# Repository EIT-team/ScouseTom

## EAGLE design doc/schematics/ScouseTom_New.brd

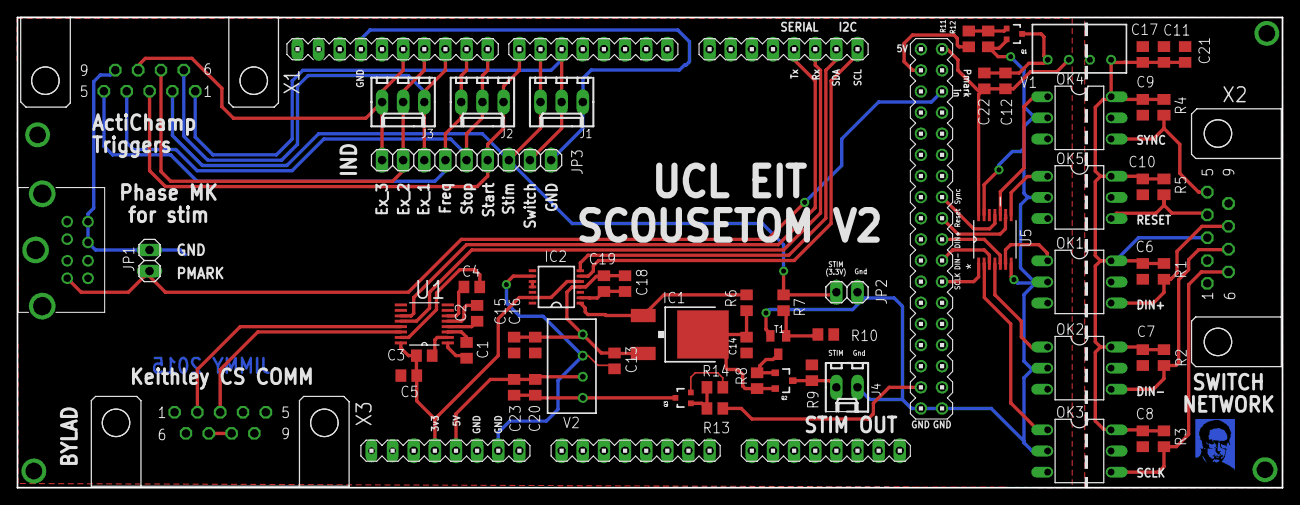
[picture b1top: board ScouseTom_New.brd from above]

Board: 2 copper layers, 152.0 x 56.5 mm, 64 parts (0 on the bottom side), 55 nets.

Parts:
C1, C2, C3, C4, C5, C6, C7, C8, C9, C10, C12, C13, C16, C17, C18, C20: 0.1uF; C0805
C11, C15, C21: 47uF; C0805
C14: 1uF; C0805
C19, C22, C23: 10uF; C0805
DIN8: CS_TRIGGERLINK; DIN8
DUE: DUE(NOMID)
IC1: LM317MBDT; DPACK
IC2: AD5280; TSSOP14
J1: Ind main; 6410-03
J2: Ind Ex1; 6410-03
J3: Ind Ex2; 6410-03
J4: Stim out; 6410-02
JP1: PMARK; 1X02
JP2: Ext Stim; 1X02
JP3: IND_BK; 1X09
OK1, OK2, OK3, OK4, OK5: H11L3M; DIL06
Q1, Q3: FDV303N; SOT323
Q2: FDN304P; SOT23-3
R1, R2, R3: 270; R0805
R4, R5: 270; M0805
R6: 470; R0805
R7: 33k; R0805
R8: 5K1; R0805
R9: 3k; R0805
R10, R12, R14: 10k; R0805
R11, R13: 330; R0805
T1: BC817; SOT23-BEC
U1: ADM3202ARUZ; SOP65P640X120-16N
U5: SN74HCT14PWT; SOP65P640X120-14N
V1: TME0505S; TME
V2: TME1205S; TME
X1: IND DSUB; DSUB9
X2: SW DSUB; DSUB9
X3: CS DSUB; DSUB9

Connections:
5VA: C6.1, C7.1, C8.1, C9.1, C10.1, C11.1, C17.2, C21.1, OK1.6, OK2.6, OK3.6, OK4.6, OK5.6, R1.2, R2.2, R3.2, R4.2, R5.2, V1.4, X2.3
5V_SIDE: C20.2, C23.1, DUE.5V, V2.2
+3V3: C3.1, C5.1, DUE.3V3, IC2.5, IC2.13, U1.16
+5V: C12.2, C22.1, DUE.5V_B, U5.14, V1.2
AGND: C6.2, C7.2, C8.2, C9.2, C10.2, C11.2, C17.1, C21.2, OK1.5, OK2.5, OK3.5, OK4.5, OK5.5, V1.3, X2.2
CS_PMARK: DIN8.3, DUE.25, JP1.2
DIN+: OK1.4, R1.1, X2.8
DIN+_ARD: DUE.39, U5.5
DIN+_INV: OK1.1, U5.6
DIN-: OK2.4, R2.1, X2.7
DIN-_ARD: DUE.41, U5.3
DIN-_INV: OK2.1, U5.4
GND: C4.2, C5.2, C13.1, C14.1, C15.2, C16.1, C18.1, C19.2, DIN8.7, DIN8.8, DUE.GND1, DUE.GND_1, DUE.GND_2, DUE.GND_A, DUE.GND_B, IC2.2, IC2.8, IC2.9, IC2.10, IC2.11, J1.3, J4.2, JP1.1, JP2.2, JP3.9, OK1.2, OK2.2, OK3.2, OK4.2, OK5.2, Q1.2, Q3.2, R9.1, R10.1, R12.1, R14.1, T1.E, U1.15, U5.7, U5.13, V2.3, X1.9, X3.5
IND_EX_1: DUE.10, J3.3, JP3.3, X1.6
IND_EX_2: DUE.11, J3.2, JP3.2, X1.7
IND_EX_3: DUE.12, J3.1, JP3.1, X1.8
IND_FREQ: DUE.9, J2.1, JP3.4, X1.5
IND_START: DUE.7, J2.3, JP3.6, X1.3
IND_STIM: DUE.6, J1.1, JP2.1, JP3.7, R7.1, X1.2
IND_STOP: DUE.8, J2.2, JP3.5, X1.4
IND_SWITCH: DUE.5, J1.2, JP3.8, X1.1
unnamed: R7.2, R10.2, T1.B
unnamed: Q1.1, R11.1, R12.2
unnamed: Q2.1, R8.2, T1.C
unnamed: X3.7, X3.8
unnamed: Q3.1, R13.1, R14.2
unnamed: C1.2, U1.1
unnamed: C1.1, U1.3
unnamed: C2.2, U1.4
unnamed: C2.1, U1.5
unnamed: C3.2, U1.2
unnamed: C4.1, U1.6
POT_IN: IC1.1, IC2.1, R6.2
PWR_STIM: DUE.52, R13.2
PWR_SWITCH: DUE.22, R11.2
RESET: OK5.4, R5.1, X2.4
RESET_ARD: DUE.37, U5.9
RESET_INV: OK5.1, U5.8
RS232_RXD: U1.14, X3.3
RS232_TXD: U1.13, X3.2
SCL: DUE.SCL, IC2.6
SCLK: OK3.4, R3.1, X2.6
SCLK_ARD: DUE.43, U5.1
SCLK_INV: OK3.1, U5.2
SDA: DUE.SDA, IC2.7
STIM_OUT: J4.1, Q2.3, R9.2
STIM_REG_VIN-: C20.1, C23.2, Q3.3, V2.1
SW_REG_VIN-: C12.1, C22.2, Q1.3, V1.1
SYNC: OK4.4, R4.1, X2.5
SYNC_ARD: DUE.35, U5.11
SYNC_INV: OK4.1, U5.10
TTL_RX: DUE.RX1, U1.12
TTL_TX: DUE.TX1, U1.11
V_STIM: C14.2, IC1.4, Q2.2, R6.1, R8.1
V_STIM_REF: C13.2, C15.1, C16.2, C18.2, C19.1, IC1.3, IC2.4, V2.4

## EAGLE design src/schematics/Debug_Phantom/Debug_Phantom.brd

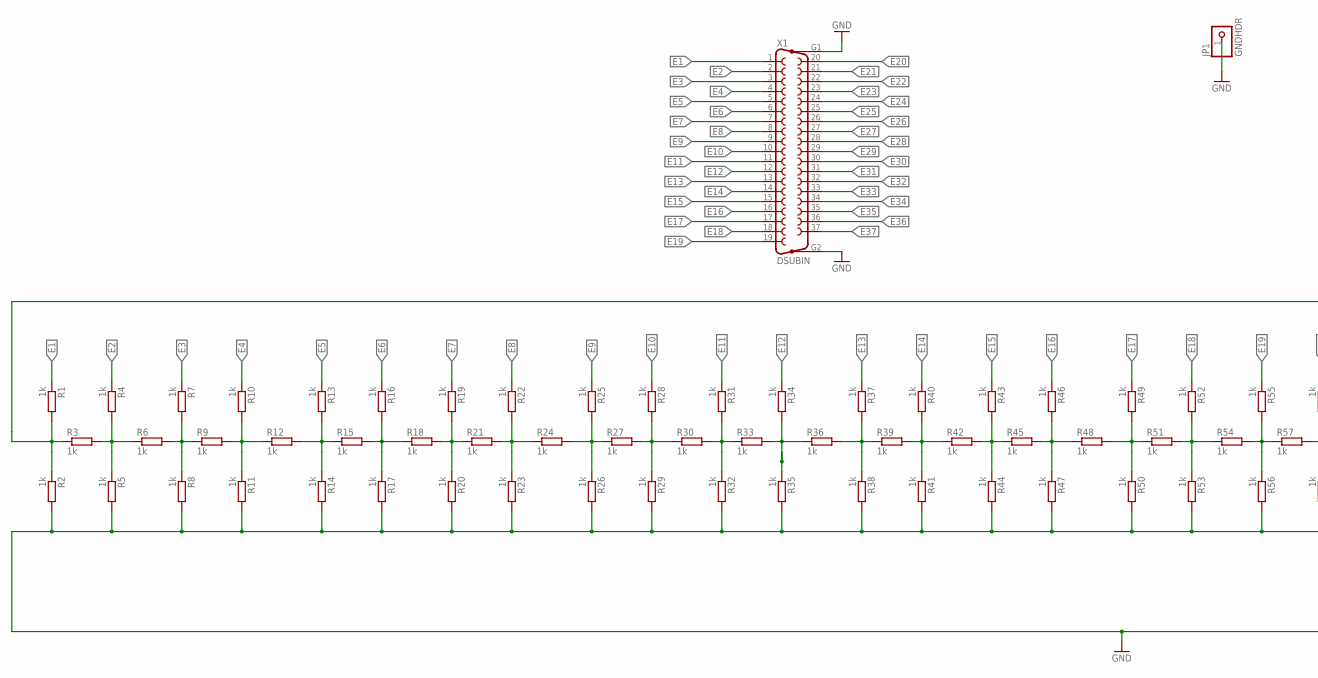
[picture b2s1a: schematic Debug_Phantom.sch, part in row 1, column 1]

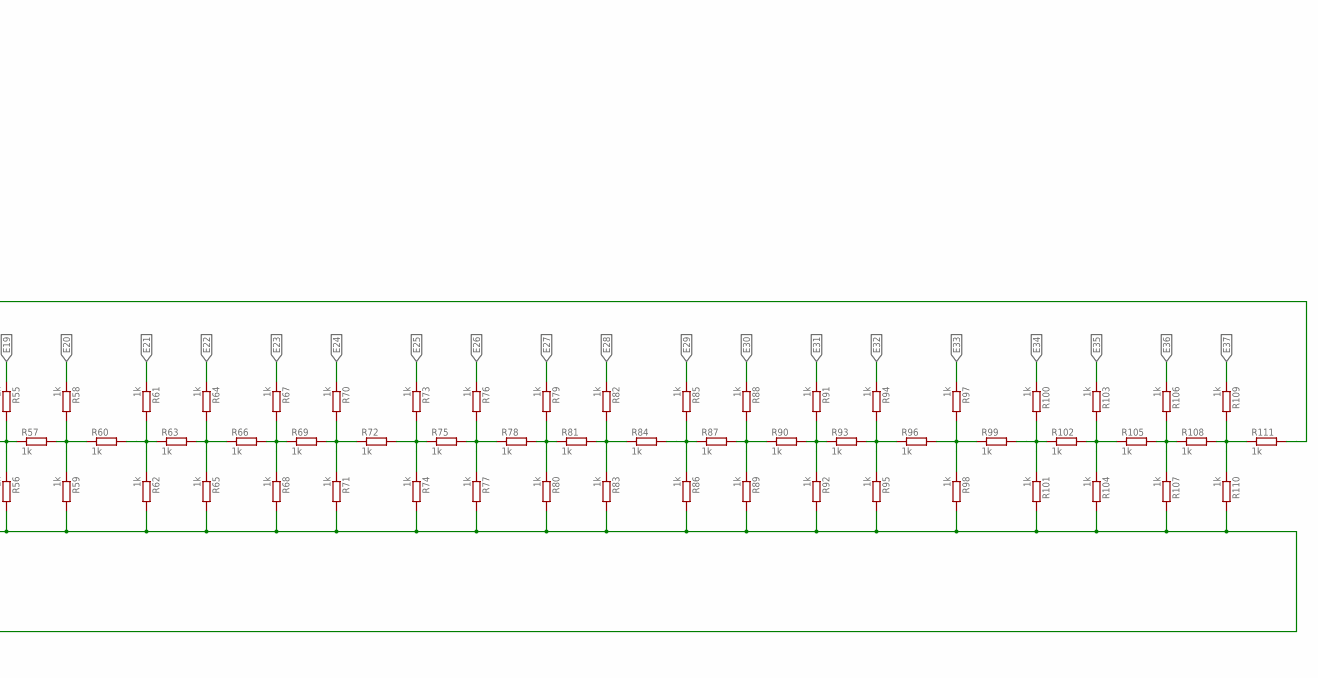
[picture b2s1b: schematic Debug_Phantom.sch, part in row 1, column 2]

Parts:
JP1: GNDHDR; 1X01
R1, R2, R3, R4, R5, R6, R7, R8, R9, R10, R11, R12, R13, R14, R15, R16, R17, R18, R19, R20, R21, R22, R23, R24, R25, R26, R27, R28, R29, R30, R31, R32, R33, R34, R35, R36, R37, R38, R39, R40, R41, R42, R43, R44, R45, R46, R47, R48, R49, R50, R51, R52, R53, R54, R55, R56, R57, R58, R59, R60, R61, R62, R63, R64, R65, R66, R67, R68, R69, R70, R71, R72, R73, R74, R75, R76, R77, R78, R79, R80, R81, R82, R83, R84, R85, R86, R87, R88, R89, R90, R91, R92, R93, R94, R95, R96, R97, R98, R99, R100, R101, R102, R103, R104, R105, R106, R107, R108, R109, R110, R111: 1k; R0402
X1: DSUBIN; F37VP

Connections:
E1: R1.1, X1.1
E2: R4.1, X1.2
E3: R7.1, X1.3
E4: R10.1, X1.4
E5: R13.1, X1.5
E6: R16.1, X1.6
E7: R19.1, X1.7
E8: R22.1, X1.8
E9: R25.1, X1.9
E10: R28.1, X1.10
E11: R31.1, X1.11
E12: R34.1, X1.12
E13: R37.1, X1.13
E14: R40.1, X1.14
E15: R43.1, X1.15
E16: R46.1, X1.16
E17: R49.1, X1.17
E18: R52.1, X1.18
E19: R55.1, X1.19
E20: R58.1, X1.20
E21: R61.1, X1.21
E22: R64.1, X1.22
E23: R67.1, X1.23
E24: R70.1, X1.24
E25: R73.1, X1.25
E26: R76.1, X1.26
E27: R79.1, X1.27
E28: R82.1, X1.28
E29: R85.1, X1.29
E30: R88.1, X1.30
E31: R91.1, X1.31
E32: R94.1, X1.32
E33: R97.1, X1.33
E34: R100.1, X1.34
E35: R103.1, X1.35
E36: R106.1, X1.36
E37: R109.1, X1.37
E38: R1.2, R2.1, R3.1, R111.2
E39: R3.2, R4.2, R5.1, R6.1
E40: R6.2, R7.2, R8.1, R9.1
E41: R9.2, R10.2, R11.1, R12.1
E42: R12.2, R13.2, R14.1, R15.1
E43: R15.2, R16.2, R17.1, R18.1
E44: R18.2, R19.2, R20.1, R21.1
E45: R21.2, R22.2, R23.1, R24.1
E46: R24.2, R25.2, R26.1, R27.1
E47: R27.2, R28.2, R29.1, R30.1
E48: R30.2, R31.2, R32.1, R33.1
E49: R33.2, R34.2, R35.1, R36.1
E50: R36.2, R37.2, R38.1, R39.1
E51: R39.2, R40.2, R41.1, R42.1
E52: R42.2, R43.2, R44.1, R45.1
E53: R45.2, R46.2, R47.1, R48.1
E54: R48.2, R49.2, R50.1, R51.1
E55: R51.2, R52.2, R53.1, R54.1
E56: R54.2, R55.2, R56.1, R57.1
E57: R57.2, R58.2, R59.1, R60.1
E58: R60.2, R61.2, R62.1, R63.1
E59: R63.2, R64.2, R65.1, R66.1
E60: R66.2, R67.2, R68.1, R69.1
E61: R69.2, R70.2, R71.1, R72.1
E63: R75.2, R76.2, R77.1, R78.1
E64: R78.2, R79.2, R80.1, R81.1
E65: R81.2, R82.2, R83.1, R84.1
E66: R84.2, R85.2, R86.1, R87.1
E67: R87.2, R88.2, R89.1, R90.1
E68: R90.2, R91.2, R92.1, R93.1
E69: R93.2, R94.2, R95.1, R96.1
E70: R96.2, R97.2, R98.1, R99.1
E72: R102.2, R103.2, R104.1, R105.1
E73: R105.2, R106.2, R107.1, R108.1
E74: R108.2, R109.2, R110.1, R111.1
GND: JP1.1, R2.2, R5.2, R8.2, R11.2, R14.2, R17.2, R20.2, R23.2, R26.2, R29.2, R32.2, R35.2, R38.2, R41.2, R44.2, R47.2, R50.2, R53.2, R56.2, R59.2, R62.2, R65.2, R68.2, R71.2, R74.2, R77.2, R80.2, R83.2, R86.2, R89.2, R92.2, R95.2, R98.2, R101.2, R104.2, R107.2, R110.2, X1.G1, X1.G2
unnamed: R72.2, R73.2, R74.1, R75.1
unnamed: R99.2, R100.2, R101.1, R102.1

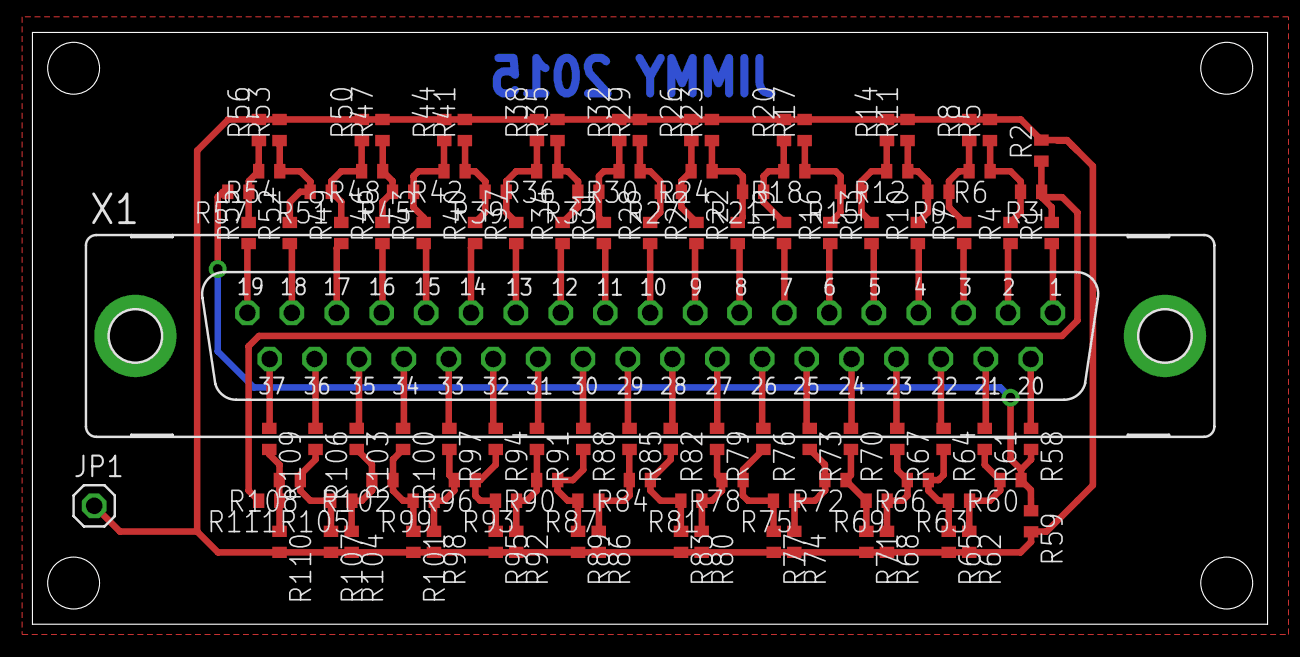
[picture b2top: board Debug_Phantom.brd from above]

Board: 2 copper layers, 76.2 x 36.5 mm, 113 parts (0 on the bottom side), 75 nets.

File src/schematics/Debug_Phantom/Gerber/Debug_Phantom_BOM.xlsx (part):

Part | Value | Device | Package | Description | MPN | OC_FARNELL | PCBTRAINFREE
R1 | 1k | R-EU_R0402 | R0402 | RESISTOR, European symbol | MC00625W040211K | 1358043 | PCBTRAINFREESTOCK
R2 | 1k | R-EU_R0402 | R0402 | RESISTOR, European symbol | MC00625W040211K | 1358043 | PCBTRAINFREESTOCK
R3 | 1k | R-EU_R0402 | R0402 | RESISTOR, European symbol | MC00625W040211K | 1358043 | PCBTRAINFREESTOCK
R4 | 1k | R-EU_R0402 | R0402 | RESISTOR, European symbol | MC00625W040211K | 1358043 | PCBTRAINFREESTOCK
R5 | 1k | R-EU_R0402 | R0402 | RESISTOR, European symbol | MC00625W040211K | 1358043 | PCBTRAINFREESTOCK
R6 | 1k | R-EU_R0402 | R0402 | RESISTOR, European symbol | MC00625W040211K | 1358043 | PCBTRAINFREESTOCK
R7 | 1k | R-EU_R0402 | R0402 | RESISTOR, European symbol | MC00625W040211K | 1358043 | PCBTRAINFREESTOCK
R8 | 1k | R-EU_R0402 | R0402 | RESISTOR, European symbol | MC00625W040211K | 1358043 | PCBTRAINFREESTOCK
R9 | 1k | R-EU_R0402 | R0402 | RESISTOR, European symbol | MC00625W040211K | 1358043 | PCBTRAINFREESTOCK
R10 | 1k | R-EU_R0402 | R0402 | RESISTOR, European symbol | MC00625W040211K | 1358043 | PCBTRAINFREESTOCK
R11 | 1k | R-EU_R0402 | R0402 | RESISTOR, European symbol | MC00625W040211K | 1358043 | PCBTRAINFREESTOCK
R12 | 1k | R-EU_R0402 | R0402 | RESISTOR, European symbol | MC00625W040211K | 1358043 | PCBTRAINFREESTOCK
R13 | 1k | R-EU_R0402 | R0402 | RESISTOR, European symbol | MC00625W040211K | 1358043 | PCBTRAINFREESTOCK
R14 | 1k | R-EU_R0402 | R0402 | RESISTOR, European symbol | MC00625W040211K | 1358043 | PCBTRAINFREESTOCK
R15 | 1k | R-EU_R0402 | R0402 | RESISTOR, European symbol | MC00625W040211K | 1358043 | PCBTRAINFREESTOCK
R16 | 1k | R-EU_R0402 | R0402 | RESISTOR, European symbol | MC00625W040211K | 1358043 | PCBTRAINFREESTOCK
R17 | 1k | R-EU_R0402 | R0402 | RESISTOR, European symbol | MC00625W040211K | 1358043 | PCBTRAINFREESTOCK
R18 | 1k | R-EU_R0402 | R0402 | RESISTOR, European symbol | MC00625W040211K | 1358043 | PCBTRAINFREESTOCK
R19 | 1k | R-EU_R0402 | R0402 | RESISTOR, European symbol | MC00625W040211K | 1358043 | PCBTRAINFREESTOCK
R20 | 1k | R-EU_R0402 | R0402 | RESISTOR, European symbol | MC00625W040211K | 1358043 | PCBTRAINFREESTOCK
R21 | 1k | R-EU_R0402 | R0402 | RESISTOR, European symbol | MC00625W040211K | 1358043 | PCBTRAINFREESTOCK
R22 | 1k | R-EU_R0402 | R0402 | RESISTOR, European symbol | MC00625W040211K | 1358043 | PCBTRAINFREESTOCK
R23 | 1k | R-EU_R0402 | R0402 | RESISTOR, European symbol | MC00625W040211K | 1358043 | PCBTRAINFREESTOCK
R24 | 1k | R-EU_R0402 | R0402 | RESISTOR, European symbol | MC00625W040211K | 1358043 | PCBTRAINFREESTOCK
R25 | 1k | R-EU_R0402 | R0402 | RESISTOR, European symbol | MC00625W040211K | 1358043 | PCBTRAINFREESTOCK
R26 | 1k | R-EU_R0402 | R0402 | RESISTOR, European symbol | MC00625W040211K | 1358043 | PCBTRAINFREESTOCK
R27 | 1k | R-EU_R0402 | R0402 | RESISTOR, European symbol | MC00625W040211K | 1358043 | PCBTRAINFREESTOCK
R28 | 1k | R-EU_R0402 | R0402 | RESISTOR, European symbol | MC00625W040211K | 1358043 | PCBTRAINFREESTOCK
R29 | 1k | R-EU_R0402 | R0402 | RESISTOR, European symbol | MC00625W040211K | 1358043 | PCBTRAINFREESTOCK
R30 | 1k | R-EU_R0402 | R0402 | RESISTOR, European symbol | MC00625W040211K | 1358043 | PCBTRAINFREESTOCK
R31 | 1k | R-EU_R0402 | R0402 | RESISTOR, European symbol | MC00625W040211K | 1358043 | PCBTRAINFREESTOCK
R32 | 1k | R-EU_R0402 | R0402 | RESISTOR, European symbol | MC00625W040211K | 1358043 | PCBTRAINFREESTOCK
R33 | 1k | R-EU_R0402 | R0402 | RESISTOR, European symbol | MC00625W040211K | 1358043 | PCBTRAINFREESTOCK
R34 | 1k | R-EU_R0402 | R0402 | RESISTOR, European symbol | MC00625W040211K | 1358043 | PCBTRAINFREESTOCK
R35 | 1k | R-EU_R0402 | R0402 | RESISTOR, European symbol | MC00625W040211K | 1358043 | PCBTRAINFREESTOCK
R36 | 1k | R-EU_R0402 | R0402 | RESISTOR, European symbol | MC00625W040211K | 1358043 | PCBTRAINFREESTOCK
R37 | 1k | R-EU_R0402 | R0402 | RESISTOR, European symbol | MC00625W040211K | 1358043 | PCBTRAINFREESTOCK
R38 | 1k | R-EU_R0402 | R0402 | RESISTOR, European symbol | MC00625W040211K | 1358043 | PCBTRAINFREESTOCK
R39 | 1k | R-EU_R0402 | R0402 | RESISTOR, European symbol | MC00625W040211K | 1358043 | PCBTRAINFREESTOCK
R40 | 1k | R-EU_R0402 | R0402 | RESISTOR, European symbol | MC00625W040211K | 1358043 | PCBTRAINFREESTOCK
R41 | 1k | R-EU_R0402 | R0402 | RESISTOR, European symbol | MC00625W040211K | 1358043 | PCBTRAINFREESTOCK
R42 | 1k | R-EU_R0402 | R0402 | RESISTOR, European symbol | MC00625W040211K | 1358043 | PCBTRAINFREESTOCK
R43 | 1k | R-EU_R0402 | R0402 | RESISTOR, European symbol | MC00625W040211K | 1358043 | PCBTRAINFREESTOCK
R44 | 1k | R-EU_R0402 | R0402 | RESISTOR, European symbol | MC00625W040211K | 1358043 | PCBTRAINFREESTOCK
R45 | 1k | R-EU_R0402 | R0402 | RESISTOR, European symbol | MC00625W040211K | 1358043 | PCBTRAINFREESTOCK
R46 | 1k | R-EU_R0402 | R0402 | RESISTOR, European symbol | MC00625W040211K | 1358043 | PCBTRAINFREESTOCK
R47 | 1k | R-EU_R0402 | R0402 | RESISTOR, European symbol | MC00625W040211K | 1358043 | PCBTRAINFREESTOCK
R48 | 1k | R-EU_R0402 | R0402 | RESISTOR, European symbol | MC00625W040211K | 1358043 | PCBTRAINFREESTOCK
R49 | 1k | R-EU_R0402 | R0402 | RESISTOR, European symbol | MC00625W040211K | 1358043 | PCBTRAINFREESTOCK
R50 | 1k | R-EU_R0402 | R0402 | RESISTOR, European symbol | MC00625W040211K | 1358043 | PCBTRAINFREESTOCK
R51 | 1k | R-EU_R0402 | R0402 | RESISTOR, European symbol | MC00625W040211K | 1358043 | PCBTRAINFREESTOCK
R52 | 1k | R-EU_R0402 | R0402 | RESISTOR, European symbol | MC00625W040211K | 1358043 | PCBTRAINFREESTOCK
R53 | 1k | R-EU_R0402 | R0402 | RESISTOR, European symbol | MC00625W040211K | 1358043 | PCBTRAINFREESTOCK
R54 | 1k | R-EU_R0402 | R0402 | RESISTOR, European symbol | MC00625W040211K | 1358043 | PCBTRAINFREESTOCK
R55 | 1k | R-EU_R0402 | R0402 | RESISTOR, European symbol | MC00625W040211K | 1358043 | PCBTRAINFREESTOCK
R56 | 1k | R-EU_R0402 | R0402 | RESISTOR, European symbol | MC00625W040211K | 1358043 | PCBTRAINFREESTOCK
R57 | 1k | R-EU_R0402 | R0402 | RESISTOR, European symbol | MC00625W040211K | 1358043 | PCBTRAINFREESTOCK
R58 | 1k | R-EU_R0402 | R0402 | RESISTOR, European symbol | MC00625W040211K | 1358043 | PCBTRAINFREESTOCK
R59 | 1k | R-EU_R0402 | R0402 | RESISTOR, European symbol | MC00625W040211K | 1358043 | PCBTRAINFREESTOCK
R60 | 1k | R-EU_R0402 | R0402 | RESISTOR, European symbol | MC00625W040211K | 1358043 | PCBTRAINFREESTOCK
R61 | 1k | R-EU_R0402 | R0402 | RESISTOR, European symbol | MC00625W040211K | 1358043 | PCBTRAINFREESTOCK
R62 | 1k | R-EU_R0402 | R0402 | RESISTOR, European symbol | MC00625W040211K | 1358043 | PCBTRAINFREESTOCK
R63 | 1k | R-EU_R0402 | R0402 | RESISTOR, European symbol | MC00625W040211K | 1358043 | PCBTRAINFREESTOCK
R64 | 1k | R-EU_R0402 | R0402 | RESISTOR, European symbol | MC00625W040211K | 1358043 | PCBTRAINFREESTOCK
R65 | 1k | R-EU_R0402 | R0402 | RESISTOR, European symbol | MC00625W040211K | 1358043 | PCBTRAINFREESTOCK
R66 | 1k | R-EU_R0402 | R0402 | RESISTOR, European symbol | MC00625W040211K | 1358043 | PCBTRAINFREESTOCK
R67 | 1k | R-EU_R0402 | R0402 | RESISTOR, European symbol | MC00625W040211K | 1358043 | PCBTRAINFREESTOCK
R68 | 1k | R-EU_R0402 | R0402 | RESISTOR, European symbol | MC00625W040211K | 1358043 | PCBTRAINFREESTOCK
R69 | 1k | R-EU_R0402 | R0402 | RESISTOR, European symbol | MC00625W040211K | 1358043 | PCBTRAINFREESTOCK
R70 | 1k | R-EU_R0402 | R0402 | RESISTOR, European symbol | MC00625W040211K | 1358043 | PCBTRAINFREESTOCK
R71 | 1k | R-EU_R0402 | R0402 | RESISTOR, European symbol | MC00625W040211K | 1358043 | PCBTRAINFREESTOCK
R72 | 1k | R-EU_R0402 | R0402 | RESISTOR, European symbol | MC00625W040211K | 1358043 | PCBTRAINFREESTOCK
R73 | 1k | R-EU_R0402 | R0402 | RESISTOR, European symbol | MC00625W040211K | 1358043 | PCBTRAINFREESTOCK
R74 | 1k | R-EU_R0402 | R0402 | RESISTOR, European symbol | MC00625W040211K | 1358043 | PCBTRAINFREESTOCK
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
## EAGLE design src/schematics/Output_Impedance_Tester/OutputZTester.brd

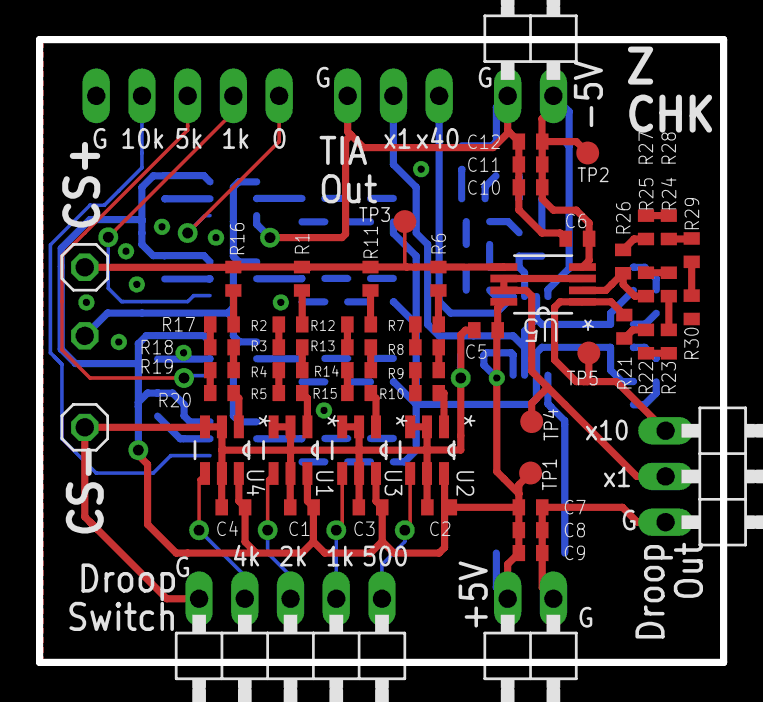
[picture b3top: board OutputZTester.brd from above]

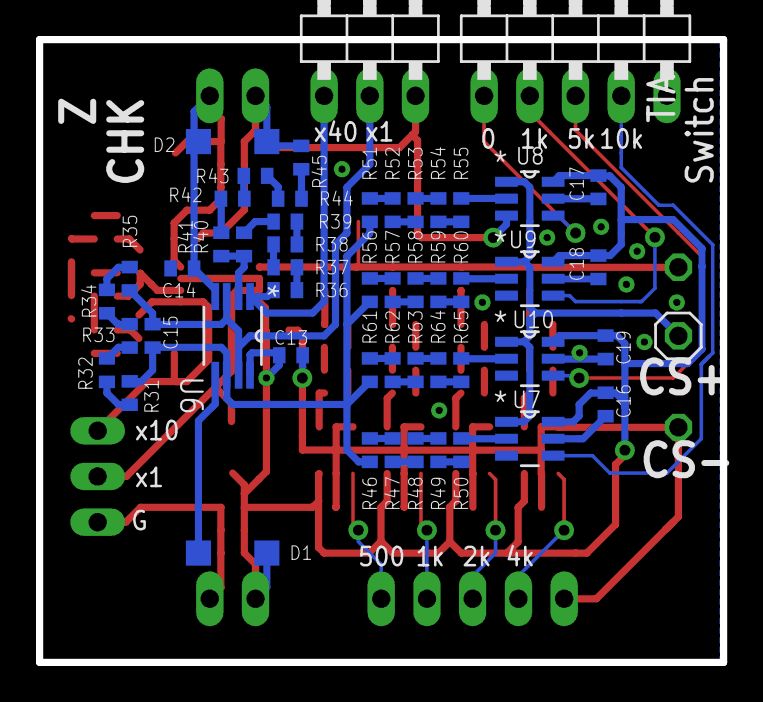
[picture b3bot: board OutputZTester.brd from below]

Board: 2 copper layers, 38.0 x 34.6 mm, 110 parts (52 on the bottom side), 80 nets.

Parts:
C1, C2, C3, C4, C5, C6, C8, C11, C13, C14, C16, C17, C18, C19: 0.1uF; C0402
C7, C10: 2.2uF; C0402
C9, C12: 10nF; C0402
C15: 2.2nF; C0402
D1, D2: 1N4148W-7-F; SOD123
JP1: Droop_out; 1X03/90
JP2: Droop_sw; 1X05/90
JP3: Source; 1X01
JP4: Sink; 1X01
JP5, JP6: PWR_IN; 1X02/90
JP7: Source_TIA; 1X01
JP8: TIA_out; 1X03/90
JP9: TIA_sw; 1X05/90
R1, R3, R5: 430; R0402
R2, R11, R12, R13, R14, R15, R31, R32, R33, R34, R35, R56, R57, R58, R59, R60: 200; R0402
R4: 510; R0402
R6, R7, R8, R9, R10: 100; R0402
R16, R17, R18, R19: 750; R0402
R20: 1000; R0402
R21, R22, R23, R24, R25, R46, R47, R48, R49, R50: 2k; R0402
R26, R27, R28, R29, R30: 20k; R0402
R36, R37, R38, R39, R40: 12k; R0402
R41, R42, R43, R44, R45: 300; R0402
R51, R52, R53, R54, R55: 0; R0402
R61, R62, R63, R64, R65: 1k; R0402
TP1, TP2, TP3, TP4, TP5: TPSB1,27; B1,27
U1, U2, U3, U4, U7, U8, U9, U10: ADG801BRTZ-REEL7; SOT95P280X145-6N
U5, U6: ADA4552-2ARM; SOP65P490X110-8N

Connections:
AGND: C1.1, C2.1, C3.1, C4.1, C5.1, C6.2, C7.2, C8.2, C9.2, C10.2, C11.2, C12.2, C13.1, C14.2, C16.1, C17.1, C18.1, C19.1, D1.A, D2.C, JP1.3, JP2.5, JP4.1, JP5.1, JP6.1, JP8.3, JP9.5, R30.1, R45.1, U1.2, U1.3, U1.5, U2.2, U2.3, U2.5, U3.2, U3.3, U3.5, U4.2, U4.3, U4.5, U6.5, U7.3, U7.5, U8.3, U8.5, U9.3, U9.5, U10.3, U10.5
unnamed: R36.2, R37.2
unnamed: R21.2, R22.2
unnamed: R22.1, R23.1
unnamed: R23.2, R24.2
unnamed: R24.1, R25.1
unnamed: R11.2, R12.2
unnamed: R29.2, R30.2
unnamed: R28.1, R29.1
unnamed: R27.2, R28.2
unnamed: R26.1, R27.1
unnamed: R12.1, R13.1
unnamed: R13.2, R14.2
unnamed: R14.1, R15.1
unnamed: R15.2, U3.1
unnamed: R1.2, R2.2
unnamed: R2.1, R3.1
unnamed: R3.2, R4.2
unnamed: R4.1, R5.1
unnamed: R5.2, U1.1
unnamed: R16.2, R17.2
unnamed: R17.1, R18.1
unnamed: R18.2, R19.2
unnamed: R19.1, R20.1
unnamed: R20.2, U4.1
unnamed: R37.1, R38.1
unnamed: R6.2, R7.2
unnamed: R7.1, R8.1
unnamed: R8.2, R9.2
unnamed: R9.1, R10.1
unnamed: R38.2, R39.2
unnamed: R10.2, U2.1
unnamed: R39.1, R40.1
unnamed: R44.2, R45.2
unnamed: R43.1, R44.1
unnamed: R42.2, R43.2
unnamed: R41.1, R42.1
unnamed: R31.2, R32.2
unnamed: R32.1, R33.1
unnamed: R33.2, R34.2
unnamed: R34.1, R35.1
unnamed: R51.2, R52.2
unnamed: R52.1, R53.1
unnamed: R53.2, R54.2
unnamed: R54.1, R55.1
unnamed: R55.2, U8.2
unnamed: R56.2, R57.2
unnamed: R57.1, R58.1
unnamed: R58.2, R59.2
unnamed: R59.1, R60.1
unnamed: R60.2, U9.2
unnamed: R61.2, R62.2
unnamed: R62.1, R63.1
unnamed: R63.2, R64.2
unnamed: R64.1, R65.1
unnamed: R65.2, U10.2
unnamed: R46.2, R47.2
unnamed: R47.1, R48.1
unnamed: R48.2, R49.2
unnamed: R49.1, R50.1
unnamed: R50.2, U7.2
SOURCE_TIA: JP7.1, U7.1, U8.1, U9.1, U10.1
SW1_PARA: JP2.1, U2.4
SW1_TIA: JP9.1, U8.4
SW2_PARA: JP2.2, U3.4
SW2_TIA: JP9.2, U9.4
SW3_PARA: JP2.3, U1.4
SW3_TIA: JP9.3, U10.4
SW4_PARA: JP2.4, U4.4
SW4_TIA: JP9.4, U7.4
V+: C1.2, C2.2, C3.2, C4.2, C5.2, C7.1, C8.1, C9.1, C13.2, C16.2, C17.2, C18.2, C19.2, D1.C, JP5.2, TP1.TP, U1.6, U2.6, U3.6, U4.6, U5.8, U6.8, U7.6, U8.6, U9.6, U10.6
V-: C6.1, C10.1, C11.1, C12.1, C14.1, D2.A, JP6.2, TP2.TP, U5.4, U6.4
VAMP_PARA: JP1.1, R21.1, TP5.TP, U5.1
VAMP_TIA: JP8.1, R36.1, U6.1
VBUFF: JP1.2, TP4.TP, U5.3, U5.6, U5.7
VF_PARA: R25.2, R26.2, U5.2
VF_TIA: R40.2, R41.2, U6.2
VLOAD_PARA: JP3.1, R1.1, R6.1, R11.1, R16.1, TP3.TP, U5.5
VLOAD_TIA: C15.1, R31.1, R46.1, R51.1, R56.1, R61.1, U6.6
VOUT_TIA: C15.2, JP8.2, R35.2, U6.3, U6.7

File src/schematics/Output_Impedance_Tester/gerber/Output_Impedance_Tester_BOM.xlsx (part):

Part | Value | Device | Package | Description | MPN | OC_FARNELL | PCBTRAINFREE
C1 | 0.1uF | C-EUC0402 | C0402 | CAPACITOR, European symbol | MC0402B104K160CT | 1758896 | yes
C2 | 0.1uF | C-EUC0402 | C0402 | CAPACITOR, European symbol | MC0402B104K160CT | 1758896 | yes
C3 | 0.1uF | C-EUC0402 | C0402 | CAPACITOR, European symbol | MC0402B104K160CT | 1758896 | yes
C4 | 0.1uF | C-EUC0402 | C0402 | CAPACITOR, European symbol | MC0402B104K160CT | 1758896 | yes
C5 | 0.1uF | C-EUC0402 | C0402 | CAPACITOR, European symbol | MC0402B104K160CT | 1758896 | yes
C6 | 0.1uF | C-EUC0402 | C0402 | CAPACITOR, European symbol | MC0402B104K160CT | 1758896 | yes
C7 | 2.2uF | C-EUC0402 | C0402 | CAPACITOR, European symbol | MC0402X225M6R3CT | 1759376 | Yes
C8 | 0.1uF | C-EUC0402 | C0402 | CAPACITOR, European symbol | MC0402B104K160CT | 1758896 | yes
C9 | 10nF | C-EUC0402 | C0402 | CAPACITOR, European symbol | MC0402B103K250CT | 1758924 | yes
C10 | 2.2uF | C-EUC0402 | C0402 | CAPACITOR, European symbol | MC0402X225M6R3CT | 1759376 | Yes
C11 | 0.1uF | C-EUC0402 | C0402 | CAPACITOR, European symbol | MC0402B104K160CT | 1758896 | yes
C12 | 10nF | C-EUC0402 | C0402 | CAPACITOR, European symbol | MC0402B103K250CT | 1758924 | yes
C13 | 0.1uF | C-EUC0402 | C0402 | CAPACITOR, European symbol | MC0402B104K160CT | 1758896 | yes
C14 | 0.1uF | C-EUC0402 | C0402 | CAPACITOR, European symbol | MC0402B104K160CT | 1758896 | yes
C15 | 2.2nF | C-EUC0402 | C0402 | CAPACITOR, European symbol | MC0402B222K500CT | 1758995 | yes
C16 | 0.1uF | C-EUC0402 | C0402 | CAPACITOR, European symbol | MC0402B104K160CT | 1758896 | yes
C17 | 0.1uF | C-EUC0402 | C0402 | CAPACITOR, European symbol | MC0402B104K160CT | 1758896 | yes
C18 | 0.1uF | C-EUC0402 | C0402 | CAPACITOR, European symbol | MC0402B104K160CT | 1758896 | yes
C19 | 0.1uF | C-EUC0402 | C0402 | CAPACITOR, European symbol | MC0402B104K160CT | 1758896 | yes
D1 | 1N4148W-7-F | DIODE-SOD123 | SOD123 | DIODE | 1N4148W-7-F | 1776392 | yes
D2 | 1N4148W-7-F | DIODE-SOD123 | SOD123 | DIODE | 1N4148W-7-F | 1776392 | yes
R1 | 430 | R-EU_R0402 | R0402 | RESISTOR, European symbol | MC00625W04021430R | 1358033 | yes
R2 | 200 | R-EU_R0402 | R0402 | RESISTOR, European symbol | MC00625W04021200R | 2130293 | yes
R3 | 430 | R-EU_R0402 | R0402 | RESISTOR, European symbol | MC00625W04021430R | 1358033 | yes
R4 | 510 | R-EU_R0402 | R0402 | RESISTOR, European symbol | MC00625W04021510R | 2130329 | yes
R5 | 430 | R-EU_R0402 | R0402 | RESISTOR, European symbol | MC00625W04021430R | 1358033 | yes
R6 | 100 | R-EU_R0402 | R0402 | RESISTOR, European symbol | MC00625W04021100R | 1358015 | yes
R7 | 100 | R-EU_R0402 | R0402 | RESISTOR, European symbol | MC00625W04021100R | 1358015 | yes
R8 | 100 | R-EU_R0402 | R0402 | RESISTOR, European symbol | MC00625W04021100R | 1358015 | yes
R9 | 100 | R-EU_R0402 | R0402 | RESISTOR, European symbol | MC00625W04021100R | 1358015 | yes
R10 | 100 | R-EU_R0402 | R0402 | RESISTOR, European symbol | MC00625W04021100R | 1358015 | yes
R11 | 200 | R-EU_R0402 | R0402 | RESISTOR, European symbol | MC00625W04021200R | 2130293 | yes
R12 | 200 | R-EU_R0402 | R0402 | RESISTOR, European symbol | MC00625W04021200R | 2130293 | yes
R13 | 200 | R-EU_R0402 | R0402 | RESISTOR, European symbol | MC00625W04021200R | 2130293 | yes
R14 | 200 | R-EU_R0402 | R0402 | RESISTOR, European symbol | MC00625W04021200R | 2130293 | yes
R15 | 200 | R-EU_R0402 | R0402 | RESISTOR, European symbol | MC00625W04021200R | 2130293 | yes
R16 | 750 | R-EU_R0402 | R0402 | RESISTOR, European symbol | MC00625W04021750R | 1358039 | yes
R17 | 750 | R-EU_R0402 | R0402 | RESISTOR, European symbol | MC00625W04021750R | 1358040 | yes
R18 | 750 | R-EU_R0402 | R0402 | RESISTOR, European symbol | MC00625W04021750R | 1358041 | yes
R19 | 750 | R-EU_R0402 | R0402 | RESISTOR, European symbol | MC00625W04021750R | 1358042 | yes
R20 | 1000 | R-EU_R0402 | R0402 | RESISTOR, European symbol | MC00625W040211K | 1358043 | yes
R21 | 2k | R-EU_R0402 | R0402 | RESISTOR, European symbol | MC00625W040212K | 2130376 | yes
R22 | 2k | R-EU_R0402 | R0402 | RESISTOR, European symbol | MC00625W040212K | 2130377 | yes
R23 | 2k | R-EU_R0402 | R0402 | RESISTOR, European symbol | MC00625W040212K | 2130378 | yes
R24 | 2k | R-EU_R0402 | R0402 | RESISTOR, European symbol | MC00625W040212K | 2130379 | yes
R25 | 2k | R-EU_R0402 | R0402 | RESISTOR, European symbol | MC00625W040212K | 2130380 | yes
R26 | 20k | R-EU_R0402 | R0402 | RESISTOR, European symbol | MC00625W0402120K | 2130457 | yes
R27 | 20k | R-EU_R0402 | R0402 | RESISTOR, European symbol | MC00625W0402120K | 2130457 | yes
R28 | 20k | R-EU_R0402 | R0402 | RESISTOR, European symbol | MC00625W0402120K | 2130457 | yes
R29 | 20k | R-EU_R0402 | R0402 | RESISTOR, European symbol | MC00625W0402120K | 2130457 | yes
R30 | 20k | R-EU_R0402 | R0402 | RESISTOR, European symbol | MC00625W0402120K | 2130457 | yes
R31 | 200 | R-EU_R0402 | R0402 | RESISTOR, European symbol | MC00625W04021200R | 2130293 | yes
R32 | 200 | R-EU_R0402 | R0402 | RESISTOR, European symbol | MC00625W04021200R | 2130293 | yes
R33 | 200 | R-EU_R0402 | R0402 | RESISTOR, European symbol | MC00625W04021200R | 2130293 | yes
R34 | 200 | R-EU_R0402 | R0402 | RESISTOR, European symbol | MC00625W04021200R | 2130293 | yes
R35 | 200 | R-EU_R0402 | R0402 | RESISTOR, European symbol | MC00625W04021200R | 2130293 | yes
R36 | 12k | R-EU_R0402 | R0402 | RESISTOR, European symbol | MC00625W0402112K | 2130437 | yes
R37 | 12k | R-EU_R0402 | R0402 | RESISTOR, European symbol | MC00625W0402112K | 2130437 | yes
R38 | 12k | R-EU_R0402 | R0402 | RESISTOR, European symbol | MC00625W0402112K | 2130437 | yes
R39 | 12k | R-EU_R0402 | R0402 | RESISTOR, European symbol | MC00625W0402112K | 2130437 | yes
R40 | 12k | R-EU_R0402 | R0402 | RESISTOR, European symbol | MC00625W0402112K | 2130437 | yes
R41 | 300 | R-EU_R0402 | R0402 | RESISTOR, European symbol | MC00625W04021300R | 2130307 | yes
R42 | 300 | R-EU_R0402 | R0402 | RESISTOR, European symbol | MC00625W04021300R | 2130308 | yes
R43 | 300 | R-EU_R0402 | R0402 | RESISTOR, European symbol | MC00625W04021300R | 2130309 | yes
R44 | 300 | R-EU_R0402 | R0402 | RESISTOR, European symbol | MC00625W04021300R | 2130310 | yes
R45 | 300 | R-EU_R0402 | R0402 | RESISTOR, European symbol | MC00625W04021300R | 2130311 | yes
R46 | 2k | R-EU_R0402 | R0402 | RESISTOR, European symbol | MC00625W040212K | 2130376 | yes
R47 | 2k | R-EU_R0402 | R0402 | RESISTOR, European symbol | MC00625W040212K | 2130377 | yes
R48 | 2k | R-EU_R0402 | R0402 | RESISTOR, European symbol | MC00625W040212K | 2130378 | yes
R49 | 2k | R-EU_R0402 | R0402 | RESISTOR, European symbol | MC00625W040212K | 2130379 | yes
R50 | 2k | R-EU_R0402 | R0402 | RESISTOR, European symbol | MC00625W040212K | 2130380 | yes
R51 | 0 | R-EU_R0402 | R0402 | RESISTOR, European symbol | MC00625W040210R | 1357983 | yes
R52 | 0 | R-EU_R0402 | R0402 | RESISTOR, European symbol | MC00625W040210R | 1357984 | yes
R53 | 0 | R-EU_R0402 | R0402 | RESISTOR, European symbol | MC00625W040210R | 1357985 | yes
R54 | 0 | R-EU_R0402 | R0402 | RESISTOR, European symbol | MC00625W040210R | 1357986 | yes
R55 | 0 | R-EU_R0402 | R0402 | RESISTOR, European symbol | MC00625W040210R | 1357987 | yes
R56 | 200 | R-EU_R0402 | R0402 | RESISTOR, European symbol | MC00625W04021200R | 2130293 | yes
R57 | 200 | R-EU_R0402 | R0402 | RESISTOR, European symbol | MC00625W04021200R | 2130294 | yes
R58 | 200 | R-EU_R0402 | R0402 | RESISTOR, European symbol | MC00625W04021200R | 2130295 | yes
R59 | 200 | R-EU_R0402 | R0402 | RESISTOR, European symbol | MC00625W04021200R | 2130296 | yes
R60 | 200 | R-EU_R0402 | R0402 | RESISTOR, European symbol | MC00625W04021200R | 2130297 | yes
R61 | 1k | R-EU_R0402 | R0402 | RESISTOR, European symbol | MC00625W040211K | 1358043 | yes
R62 | 1k | R-EU_R0402 | R0402 | RESISTOR, European symbol | MC00625W040211K | 1358043 | yes
R63 | 1k | R-EU_R0402 | R0402 | RESISTOR, European symbol | MC00625W040211K | 1358043 | yes
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
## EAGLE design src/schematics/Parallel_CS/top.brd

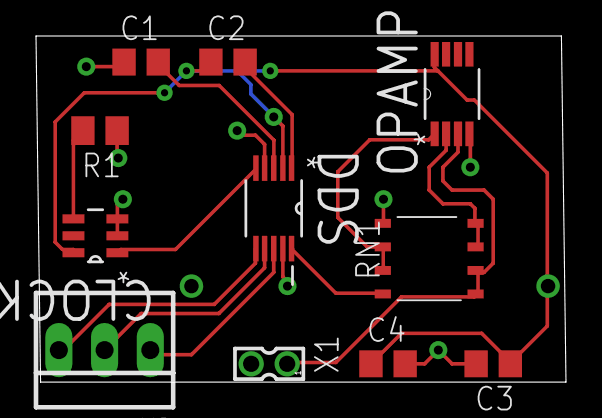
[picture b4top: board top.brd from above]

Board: 2 copper layers, 29.4 x 19.2 mm, 11 parts (0 on the bottom side), 13 nets.

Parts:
C1: 100n; C0805
C2: 10n; C0805
C3: 10u; C0805
C4: 0.1u; C0805
CLOCK: LTC6906IS6PBF; SOT95P280X100-6N
DDS: AD9833BRMZ; SOP50P490X110-10N
OPAMP: LMC6482IMM; SOP65P490X109-8N
R1: 1000k; M0805
RN1: CTS742C083
X1: 332-02
X2: 22-23-2031

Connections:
FSYNC: DDS.8, X2.1
GND: C1.1, C3.2, C4.2, CLOCK.2, CLOCK.3, DDS.4, DDS.9, OPAMP.4, R1.1, RN1.5, X1.2
unnamed: C1.2, DDS.3
unnamed: C2.2, DDS.1
unnamed: OPAMP.2, RN1.3, RN1.4
unnamed: CLOCK.1, DDS.5
unnamed: OPAMP.3, RN1.1, RN1.2, X1.1
unnamed: DDS.10, RN1.8
unnamed: OPAMP.1, RN1.6, RN1.7
unnamed: CLOCK.4, R1.2
SCLK: DDS.7, X2.2
SDATA: DDS.6, X2.3
VDD: C2.1, C3.1, C4.1, CLOCK.6, DDS.2, OPAMP.8

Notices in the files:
parts and their libraries:
SparkFun-DiscreteSemi: Licensing: Creative Commons ShareAlike 4.0 International - https://creativecommons.org/licenses/by-sa/4.0
